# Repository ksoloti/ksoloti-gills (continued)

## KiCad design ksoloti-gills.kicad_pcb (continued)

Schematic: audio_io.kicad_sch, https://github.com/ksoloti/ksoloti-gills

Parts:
J3: IN_L; Jack_6.35mm_Neutrik_NRJ6HF_Horizontal_no_screwhole
J4: IN_R; Jack_6.35mm_Neutrik_NRJ6HF_Horizontal_no_screwhole
J5: OUT_L; Jack_6.35mm_Neutrik_NRJ6HF_Horizontal_no_screwhole
J6: OUT_R; Jack_6.35mm_Neutrik_NRJ6HF_Horizontal_no_screwhole
J7: HP_OUT; Jack_6.35mm_Neutrik_NRJ6HF_Horizontal_no_screwhole
J14: HP_POT; PinHeader_2x03_P2.54mm_Vertical
J19: OUTPUT_INSERT; PinHeader_1x05_P2.54mm_Vertical
JP2: LR_NORMAL; SolderJumper-2_0603_Bridged_0_25mm
R22, R23, R24, R33: 220; R_0603_1608Metric
R25, R34, R56, R57: 47k; R_0603_1608Metric
RV11, RV12: 2*B100k; ALPS_POT_VERTICAL_PS_DUAL
TP1: OUT_L_RING; TestPoint_THTPad_D1.5mm_Drill0.7mm
TP2: OUT_R_RING; TestPoint_THTPad_D1.5mm_Drill0.7mm

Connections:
GND: RV11.7, RV12.7; also elsewhere on the board
IN_L_PIN: R56.2, RV11.2; also elsewhere on the board
IN_R_PIN: R57.2, RV11.5; also elsewhere on the board
IN_SGND_PIN: J3.S, J3.SN, J4.S, J4.SN, R56.1, R57.1, RV11.1, RV11.4; also elsewhere on the board
LHP: J7.T, J14.4, J14.6; also elsewhere on the board
MONOOUT: J7.S, J14.1, J14.2; also elsewhere on the board
unnamed: J4.T, RV11.6
unnamed: J5.R, R22.2
unnamed: J5.T, R23.2
unnamed: J6.R, R24.2
unnamed: J6.T, R33.2
unnamed: J4.TN, JP2.1 (A)
unnamed: J3.T, JP2.2 (B), RV11.3
unnamed: R22.1, TP1.1
unnamed: R23.1, R25.2, RV12.2
unnamed: R24.1, TP2.1
unnamed: R33.1, R34.2, RV12.5
OUT_L_PIN: J19.4, J19.5, RV12.3; also elsewhere on the board
OUT_R_PIN: J19.1, J19.2, RV12.6; also elsewhere on the board
OUT_SGND_PIN: J5.S, J5.SN, J6.S, J6.SN, J19.3, R25.1, R34.1, RV12.1, RV12.4; also elsewhere on the board
RHP: J7.R, J14.3, J14.5; also elsewhere on the board

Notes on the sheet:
R->
L->
HEADPHONES
output attenuator
If installing a headphone volume pot, cut bridges between pins 3&5 and 4&6!
OPTIONAL HP VOLUME
OUTPUT
INPUT
Pot "chassis"
Audio I/O
input attenuator

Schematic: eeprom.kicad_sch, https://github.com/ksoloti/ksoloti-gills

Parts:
C9: 100n; C_0603_1608Metric
U1: M24512; SOIC-8_3.9x4.9mm_P1.27mm

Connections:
+3.3V: C9.1, U1.8 (VCC); also elsewhere on the board
GND: C9.2, U1.1 (E0), U1.2 (E1), U1.3 (E2), U1.4 (VSS), U1.7 (~WC); also elsewhere on the board
PB8_GPDIO: U1.6 (SCL); also elsewhere on the board
PB9_GPDIO: U1.5 (SDA); also elsewhere on the board

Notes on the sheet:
M24512-W SOIC-8

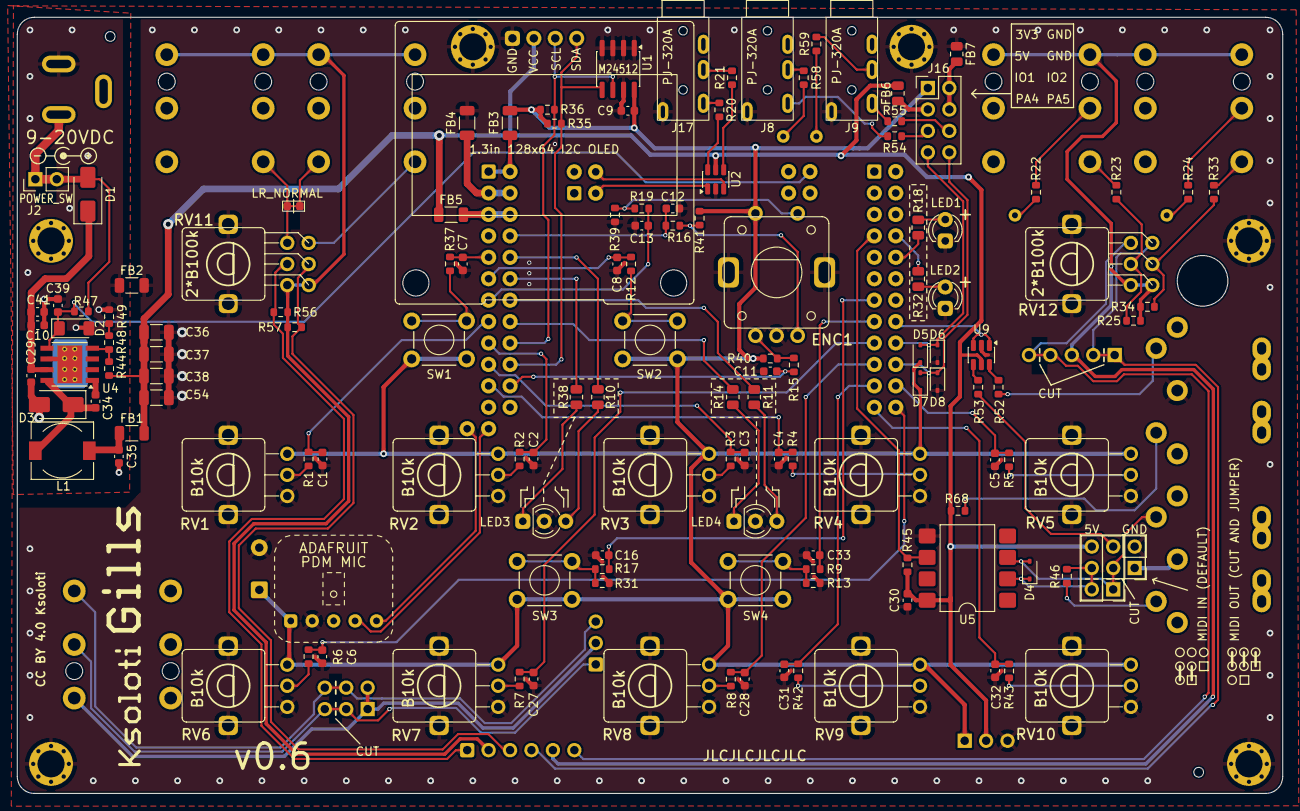
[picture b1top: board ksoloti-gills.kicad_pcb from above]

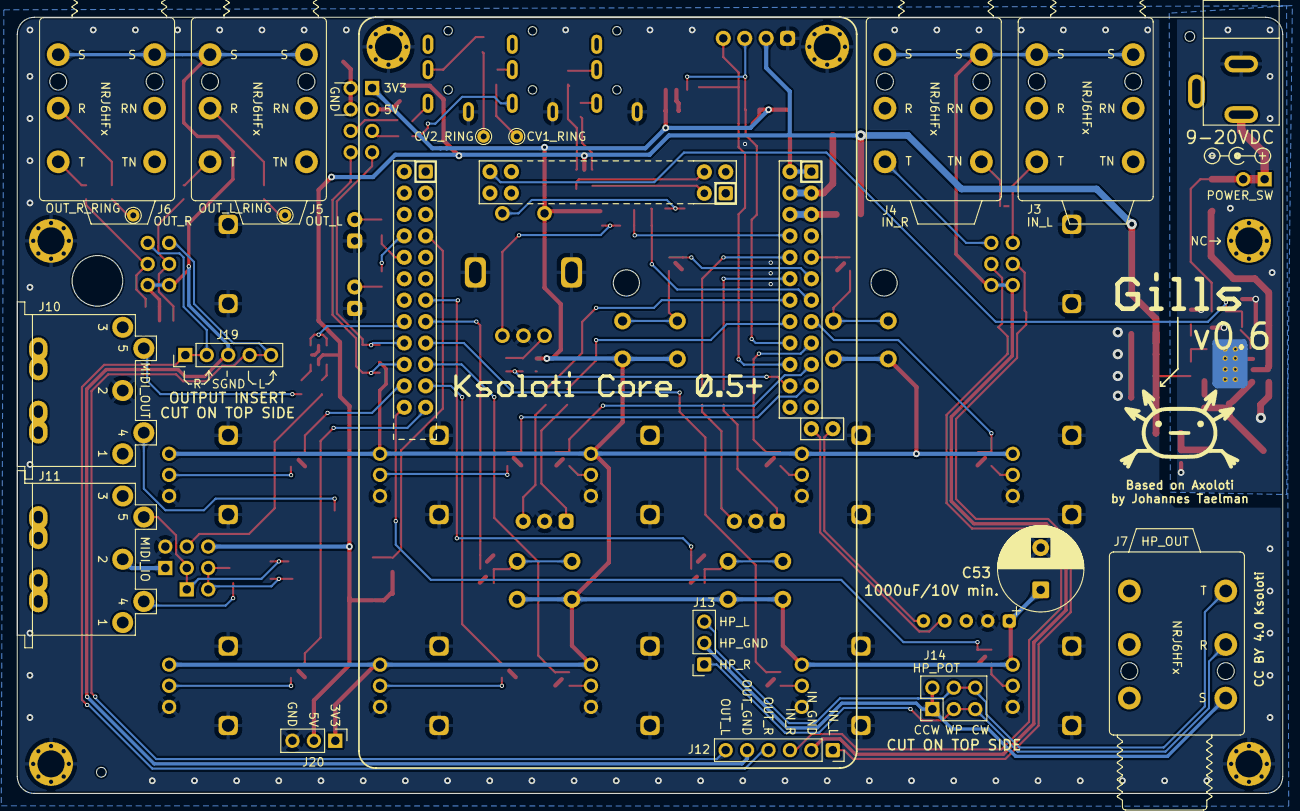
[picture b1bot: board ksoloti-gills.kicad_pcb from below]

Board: 2 copper layers, 150.0 x 92.0 mm, 224 parts (78 on the bottom side), 114 nets.

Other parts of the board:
DUMMY_CORE_3DMODEL: Symbol_Barrel_Polarity
DUMMY_CV_EXP_3DMODEL: Symbol_Barrel_Polarity
G513513: LOGO
LOGO1, LOGO2: Symbol_Barrel_Polarity

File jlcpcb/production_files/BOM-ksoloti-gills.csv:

Comment,Designator,Footprint,LCSC,Quantity
100 ohm @ 100 Mhz,"FB6,FB7",R_0805_2012Metric,C1015,2
100 ohm @ 100 Mhz,"FB1,FB2,FB3,FB4,FB5",R_1206_3216Metric,C98293,5
100n,"C11,C12,C13,C16,C29,C30,C33,C35,C39,C7,C8,C9",C_0603_1608Metric,C14663,12
10k,"R13,R31,R39,R40,R41,R44,R45",R_0603_1608Metric,C25804,7
10n,C34,C_0603_1608Metric,C57112,1
10u_25V,"C10,C41",C_0603_1608Metric,C96446,2
15uh,L1,L_7.3x6.7_H3.5,C2847544,1
1N4148WS,D4,D_SOD-323,C2128,1
1N5819WS,"D5,D6,D7,D8",D_SOD-323,C191023,4
1k,"R1,R12,R15,R16,R17,R19,R2,R3,R37,R4,R42,R43,R5,R6,R7,R8,R9",R_0603_1608Metric,C21190,17
2.2u,"C1,C2,C27,C28,C3,C31,C32,C4,C5,C6",C_0603_1608Metric,C23630,10
2.7k,"R35,R36",R_0603_1608Metric,C13167,2
220,"R20,R21,R22,R23,R24,R33,R46,R48,R52,R53,R54,R55,R58,R59,R68",R_0603_1608Metric,C22962,15
3V3,D2,D_MiniMELF,C7497475,1
3k,R49,R_0603_1608Metric,C4211,1
47k,"R25,R34,R47,R56,R57",R_0603_1608Metric,C25819,5
47u,"C36,C37,C38,C54",C_1206_3216Metric,C96123,4
6N137,U5,SMDIP-8_W9.53mm,C110020,1
74LVC2G17,"U2,U9",SOT-23-6,C10429,2
M24512,U1,SOIC-8_3.9x4.9mm_P1.27mm,C79991,1
RGREEN,"R10,R11,R18",R_0805_2012Metric,C17630,3
RRED,"R14,R32,R38",R_0805_2012Metric,C17557,3
SS34,"D1,D3",D_SMA,C8678,2
TPS5430DDA,U4,TI_SO-PowerPAD-8_ThermalVias,C9864,1
MountingHole,MH7,MountingHole_3.2mm_M3_Pad_Via_tight,,1
MountingHole,MH8,MountingHole_3.2mm_M3_Pad_Via_tight,,1
MountingHole,MH5,MountingHole_3.2mm_M3_Pad_Via_tight,,1
MountingHole,MH6,MountingHole_3.2mm_M3_Pad_Via_tight,,1
B10k,RV1,ALPS_POT_VERTICAL_PS,,1
LED_Dual_AKA,LED3,LED_D3.0mm-3_marked,,1
B10k,RV4,ALPS_POT_VERTICAL_PS,,1
LINE_IN_OUT,J12,PinSocket_1x06_P2.54mm_Vertical,,1
LED_Dual_AKA,LED4,LED_D3.0mm-3_marked,,1
B10k,RV2,ALPS_POT_VERTICAL_PS,,1
2*B100k,RV11,ALPS_POT_VERTICAL_PS_DUAL,,1
HP_POT,J14,PinHeader_2x03_P2.54mm_Vertical,,1
TL1105,SW1,TL1105T,,1
TL1105,SW4,TL1105T,,1
TL1105,SW2,TL1105T,,1
B10k,RV3,ALPS_POT_VERTICAL_PS,,1
MIDI_IO,J11,MIDI_DIN-5_DS-5-01c,,1
B10k,RV10,ALPS_POT_VERTICAL_PS,,1
B10k,RV9,ALPS_POT_VERTICAL_PS,,1
B10k,RV6,ALPS_POT_VERTICAL_PS,,1
MountingHole,MH4,MountingHole_3.2mm_M3_Pad_Via_tight,,1
2*B100k,RV12,ALPS_POT_VERTICAL_PS_DUAL,,1
RED,LED2,LED_D3.0mm_marked,,1
STEC11,ENC1,ALPS_STEC12E08,,1
B10k,RV7,ALPS_POT_VERTICAL_PS,,1
TL1105,SW3,TL1105T,,1
B10k,RV5,ALPS_POT_VERTICAL_PS,,1
MountingHole,MH1,MountingHole_3.2mm_M3_Pad_Via_tight,,1
B10k,RV8,ALPS_POT_VERTICAL_PS,,1
HP_OUT,J13,PinSocket_1x03_P2.54mm_Vertical,,1
128x64_OLED,OLED1,128x64OLED_1_3in,,1
GREEN,LED1,LED_D3.0mm_marked,,1
IN_L,J3,Jack_6.35mm_Neutrik_NRJ6HF_Horizontal_no_screwhole,,1
Conn_01x01_Female,H2_P21,PinSocket_1x01_P2.54mm_Vertical_smcrt_round,,1
Conn_01x01_Female,H1_P12,PinSocket_1x01_P2.54mm_Vertical_smcrt_round,,1
Conn_01x01_Female,H3_P2,PinSocket_1x01_P2.54mm_Vertical_smcrt_round,,1
Conn_01x01_Female,H1_P13,PinSocket_1x01_P2.54mm_Vertical_smcrt_round,,1
Conn_01x01_Female,H3_P4,PinSocket_1x01_P2.54mm_Vertical_smcrt_round,,1
Conn_01x01_Female,H1_P22,PinSocket_1x01_P2.54mm_Vertical_smcrt_round,,1
Conn_01x01_Female,H3_P17,PinSocket_1x01_P2.54mm_Vertical_smcrt_round,,1
Conn_01x01_Female,H3_P19,PinSocket_1x01_P2.54mm_Vertical_smcrt_round,,1
HP_OUT,J7,Jack_6.35mm_Neutrik_NRJ6HF_Horizontal_no_screwhole,,1
OUT_R,J6,Jack_6.35mm_Neutrik_NRJ6HF_Horizontal_no_screwhole,,1
Conn_01x01_Female,H3_P22,PinSocket_1x01_P2.54mm_Vertical_smcrt_round,,1
Conn_01x01_Female,H3_P15,PinSocket_1x01_P2.54mm_Vertical_smcrt_round,,1
EXP_IO,J8,PJ-320A_THT,,1
MIDI_OUT,J10,MIDI_DIN-5_DS-5-01c,,1
Conn_01x01_Female,H3_P23,PinSocket_1x01_P2.54mm_Vertical_smcrt_round,,1
Conn_01x01_Female,H3_P16,PinSocket_1x01_P2.54mm_Vertical_smcrt_round,,1
Conn_01x01_Female,H1_P17,PinSocket_1x01_P2.54mm_Vertical_smcrt_round,,1
Conn_01x01_Female,H3_P8,PinSocket_1x01_P2.54mm_Vertical_smcrt_round,,1
Conn_01x01_Female,H3_P14,PinSocket_1x01_P2.54mm_Vertical_smcrt_round,,1
Conn_01x01_Female,H1_P23,PinSocket_1x01_P2.54mm_Vertical_smcrt_round,,1
Conn_01x01_Female,H2_P23,PinSocket_1x01_P2.54mm_Vertical_smcrt_round,,1
Conn_01x01_Female,H3_P11,PinSocket_1x01_P2.54mm_Vertical_smcrt_round,,1
Conn_01x01_Female,H2_P22,PinSocket_1x01_P2.54mm_Vertical_smcrt_round,,1
Conn_01x01_Female,H1_P18,PinSocket_1x01_P2.54mm_Vertical_smcrt_round,,1
Conn_01x01_Female,H3_P1,PinSocket_1x01_P2.54mm_Vertical_smcrt_sqr,,1
Conn_01x01_Female,H3_P24,PinSocket_1x01_P2.54mm_Vertical_smcrt_round,,1
Conn_01x01_Female,H1_P7,PinSocket_1x01_P2.54mm_Vertical_smcrt_round,,1
Conn_01x01_Female,H3_P5,PinSocket_1x01_P2.54mm_Vertical_smcrt_round,,1
Conn_01x01_Female,H3_P20,PinSocket_1x01_P2.54mm_Vertical_smcrt_round,,1
Conn_01x01_Female,H3_P21,PinSocket_1x01_P2.54mm_Vertical_smcrt_round,,1
OUT_L,J5,Jack_6.35mm_Neutrik_NRJ6HF_Horizontal_no_screwhole,,1
Conn_01x01_Female,H1_P21,PinSocket_1x01_P2.54mm_Vertical_smcrt_round,,1
9-20VDC,J1,dc_socket,,1
Conn_01x01_Female,H1_P2,PinSocket_1x01_P2.54mm_Vertical_smcrt_round,,1
Conn_01x01_Female,H1_P19,PinSocket_1x01_P2.54mm_Vertical_smcrt_round,,1
Conn_01x01_Female,H1_P9,PinSocket_1x01_P2.54mm_Vertical_smcrt_round,,1
Conn_01x01_Female,H1_P11,PinSocket_1x01_P2.54mm_Vertical_smcrt_round,,1
Conn_01x01_Female,H3_P3,PinSocket_1x01_P2.54mm_Vertical_smcrt_round,,1
Conn_01x01_Female,H1_P10,PinSocket_1x01_P2.54mm_Vertical_smcrt_round,,1
PWR_SWITCH,J2,PinHeader_1x02_P2.54mm_Vertical,,1
Conn_01x01_Female,H1_P3,PinSocket_1x01_P2.54mm_Vertical_smcrt_round,,1
Conn_01x01_Female,H2_P24,PinSocket_1x01_P2.54mm_Vertical_smcrt_round,,1
Conn_01x01_Female,H3_P10,PinSocket_1x01_P2.54mm_Vertical_smcrt_round,,1
Conn_01x01_Female,H1_P8,PinSocket_1x01_P2.54mm_Vertical_smcrt_round,,1
Conn_01x01_Female,H3_P18,PinSocket_1x01_P2.54mm_Vertical_smcrt_round,,1
Conn_01x01_Female,H3_P7,PinSocket_1x01_P2.54mm_Vertical_smcrt_round,,1
Conn_01x01_Female,H3_P12,PinSocket_1x01_P2.54mm_Vertical_smcrt_round,,1
Conn_01x01_Female,H1_P15,PinSocket_1x01_P2.54mm_Vertical_smcrt_round,,1
EXP_IO,J9,PJ-320A_THT,,1
Conn_01x01_Female,H3_P9,PinSocket_1x01_P2.54mm_Vertical_smcrt_round,,1
Conn_01x01_Female,H1_P6,PinSocket_1x01_P2.54mm_Vertical_smcrt_round,,1
Conn_01x01_Female,H1_P20,PinSocket_1x01_P2.54mm_Vertical_smcrt_round,,1
Conn_01x01_Female,H1_P4,PinSocket_1x01_P2.54mm_Vertical_smcrt_round,,1
Conn_01x01_Female,H1_P24,PinSocket_1x01_P2.54mm_Vertical_smcrt_round,,1
IN_R,J4,Jack_6.35mm_Neutrik_NRJ6HF_Horizontal_no_screwhole,,1
Conn_01x01_Female,H3_P6,PinSocket_1x01_P2.54mm_Vertical_smcrt_round,,1
Conn_01x01_Female,H3_P13,PinSocket_1x01_P2.54mm_Vertical_smcrt_round,,1
Conn_01x01_Female,H1_P1,PinSocket_1x01_P2.54mm_Vertical_smcrt_sqr,,1
Conn_01x01_Female,H1_P14,PinSocket_1x01_P2.54mm_Vertical_smcrt_round,,1
Conn_01x01_Female,H1_P16,PinSocket_1x01_P2.54mm_Vertical_smcrt_round,,1
Conn_01x01_Female,H1_P5,PinSocket_1x01_P2.54mm_Vertical_smcrt_round,,1
LR_NORMAL,JP2,SolderJumper-2_0603_Bridged_0_25mm,,1
EXPANSION,J16,PinHeader_2x04_P2.54mm_Vertical,,1
MIDI1_CFG,J15,PinHeader_2x03_P2.54mm_Vertical,,1
MIDI_OUT_GND,J18,PinHeader_1x02_P2.54mm_Vertical,,1
2200u 10+V,C53,CP_Radial_D10.0mm_P5.00mm,,1
OUTPUT_INSERT,J19,PinHeader_1x05_P2.54mm_Vertical,,1
Adafruit_PDM_microphone_breakout,M1,Adafruit PDM microphone breakout,,1
POWER_HEADER,J20,PinHeader_1x03_P2.54mm_Vertical,,1
DMIC_CLK,H6_P2,PinSocket_1x01_P2.54mm_Vertical_smcrt_round,,1
DMIC_DAT,H6_P1,PinSocket_1x01_P2.54mm_Vertical_smcrt_round,,1
GATE_OUT,J17,PJ-320A_THT,,1
Conn_01x01_Female,H2_P4,PinSocket_1x01_P2.54mm_Vertical_smcrt_round,,1
Conn_01x01_Female,H2_P3,PinSocket_1x01_P2.54mm_Vertical_smcrt_round,,1
Conn_01x01_Female,H2_P2,PinSocket_1x01_P2.54mm_Vertical_smcrt_round,,1
Conn_01x01_Female,H2_P1,PinSocket_1x01_P2.54mm_Vertical_smcrt_sqr,,1

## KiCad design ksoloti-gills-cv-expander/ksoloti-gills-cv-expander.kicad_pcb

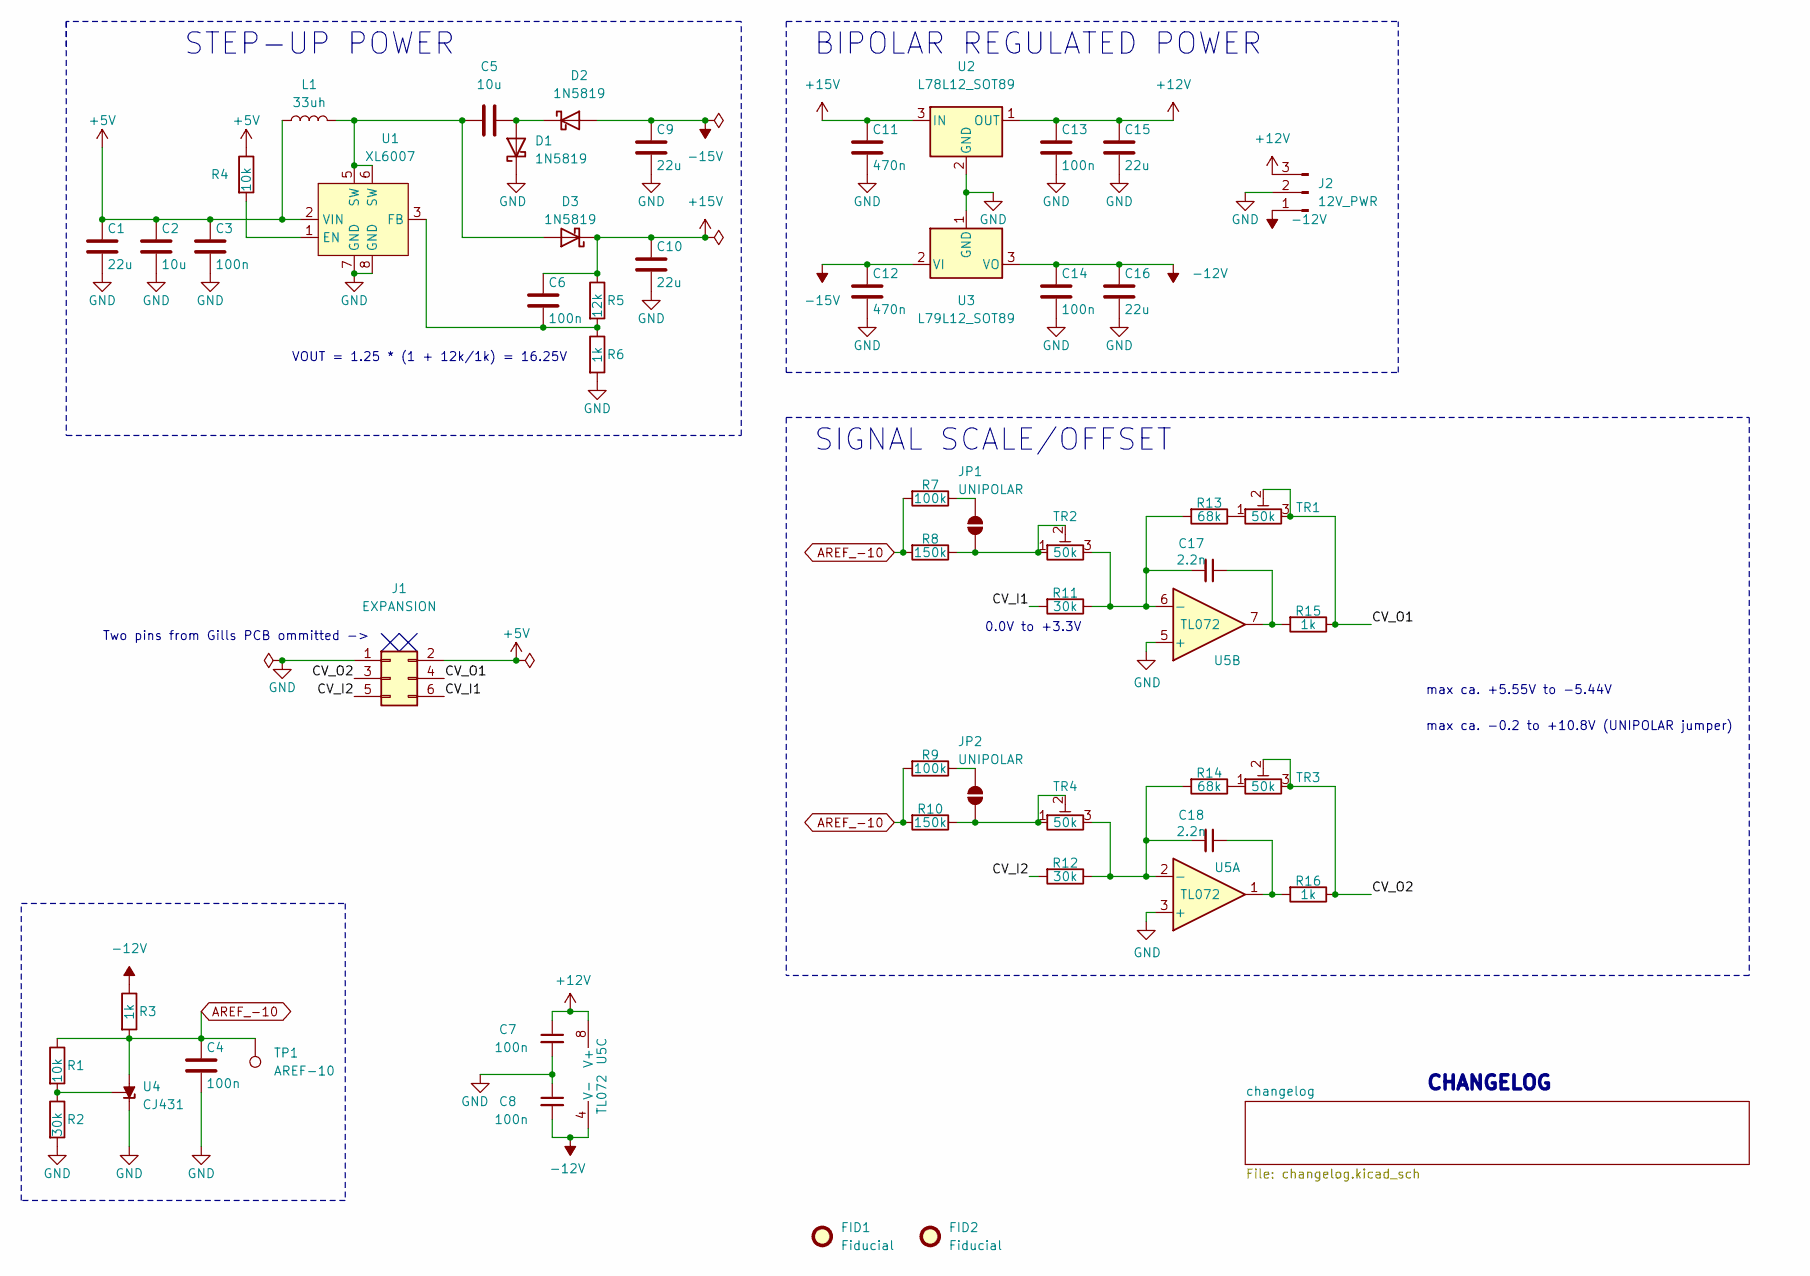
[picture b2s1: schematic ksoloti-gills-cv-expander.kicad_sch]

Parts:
C1, C9, C10, C15, C16: 22u; C_0805_2012Metric
C2, C5: 10u; C_0603_1608Metric
C3, C4, C6, C7, C8, C13, C14: 100n; C_0603_1608Metric
C11, C12: 470n; C_0603_1608Metric
C17, C18: 2.2n; C_0603_1608Metric
D1, D2, D3: 1N5819; D_SOD-323
FID1, FID2: Fiducial; jlc_tooling_hole
J1: EXPANSION; PinHeader_2x03_P2.54mm_Vertical
J2: 12V_PWR; PinHeader_1x03_P2.54mm_Vertical
JP1, JP2: UNIPOLAR; SolderJumper-2_0603_Open
L1: 33uh; L_APV_ANR5020
R1, R4: 10k; R_0603_1608Metric
R2, R11, R12: 30k; R_0603_1608Metric
R3, R6, R15, R16: 1k; R_0603_1608Metric
R5: 12k; R_0603_1608Metric
R7, R9: 100k; R_0603_1608Metric
R8, R10: 150k; R_0603_1608Metric
R13, R14: 68k; R_0603_1608Metric
TP1: AREF-10; TestPoint_THTPad_D1.0mm_Drill0.5mm
TR1, TR2, TR3, TR4: 50k; Potentiometer_Bourns_3266P_Horizontal
U1: XL6007; SOIC-8-1EP_3.9x4.9mm_P1.27mm_EP2.41x3.81mm
U2: L78L12_SOT89; SOT-89-3_clearance
U3: L79L12_SOT89; SOT-89-3_clearance
U4: CJ431; SOT-23W
U5: TL072; SOIC-8_3.9x4.9mm_P1.27mm

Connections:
+5V: C1.1, C2.1, C3.1, J1.2, L1.1, R4.1, U1.2 (VIN)
+12V: C7.1, C13.1, C15.1, J2.3, U2.1 (OUT), U5.8 (V+)
+15V: C6.1, C10.1, C11.1, D3.1 (K), R5.1, U2.3 (IN)
-12V: C8.2, C14.1, C16.1, J2.1, R3.1, U3.3 (VO), U5.4 (V-)
-15V: C9.1, C12.1, D2.2 (A), U3.2 (VI)
/CV_I1: J1.6, R11.2
/CV_I2: J1.5, R12.2
/CV_O1: J1.4, R15.1, TR1.2, TR1.3
/CV_O2: J1.3, R16.1, TR3.2, TR3.3
AREF_-10: C4.1, R1.1, R3.2, R7.2, R8.2, R9.2, R10.2, TP1.1, U4.3 (A)
GND: C1.2, C2.2, C3.2, C4.2, C7.2, C8.1, C9.2, C10.2, C11.2, C12.2, C13.2, C14.2, C15.2, C16.2, D1.1 (K), J1.1, J2.2, R2.2, R6.2, U1.7 (GND), U1.8 (GND), U1.9 (GND), U2.2 (GND), U3.1 (GND), U4.2 (K), U5.3 (+), U5.5 (+)
unnamed: C17.1, R15.2, U5.7
unnamed: C18.1, R16.2, U5.1
unnamed: C5.2, D1.2 (A), D2.1 (K)
unnamed: C5.1, D3.2 (A), L1.2, U1.5 (SW), U1.6 (SW)
unnamed: JP1.1 (A), R8.1, TR2.1, TR2.2
unnamed: JP1.2 (B), R7.1
unnamed: JP2.1 (A), R10.1, TR4.1, TR4.2
unnamed: JP2.2 (B), R9.1
unnamed: R13.1, TR1.1
unnamed: R14.1, TR3.1
unnamed: R4.2, U1.1 (EN)
unnamed: C6.2, R5.2, R6.1, U1.3 (FB)
unnamed: R1.2, R2.1, U4.1 (REF)
unnamed: C18.2, R12.1, R14.2, TR4.3, U5.2 (-)
unnamed: C17.2, R11.1, R13.2, TR2.3, U5.6 (-)

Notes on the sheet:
max ca. +5.55V to -5.44V
0.0V to +3.3V
VOUT = 1.25 * (1 + 12k/1k) = 16.25V
SIGNAL SCALE/OFFSET
STEP-UP POWER
CHANGELOG
max ca. -0.2 to +10.8V (UNIPOLAR jumper)
Two pins from Gills PCB ommitted ->
BIPOLAR REGULATED POWER

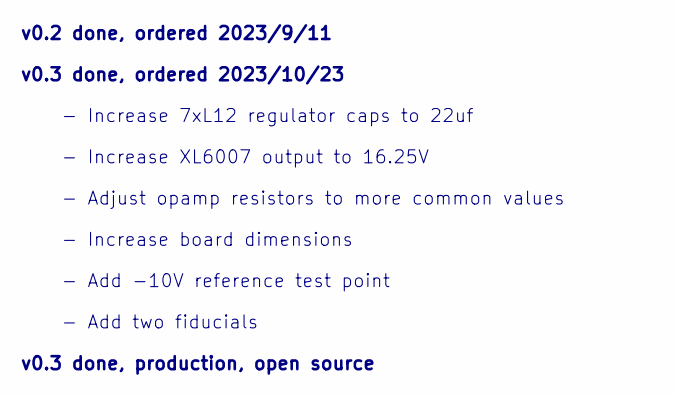
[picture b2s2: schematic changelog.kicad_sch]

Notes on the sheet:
- Increase 7xL12 regulator caps to 22uf
v0.3 done, ordered 2023/10/23
- Add -10V reference test point
- Increase XL6007 output to 16.25V
- Increase board dimensions
v0.2 done, ordered 2023/9/11
- Add two fiducials
- Adjust opamp resistors to more common values
v0.3 done, production, open source

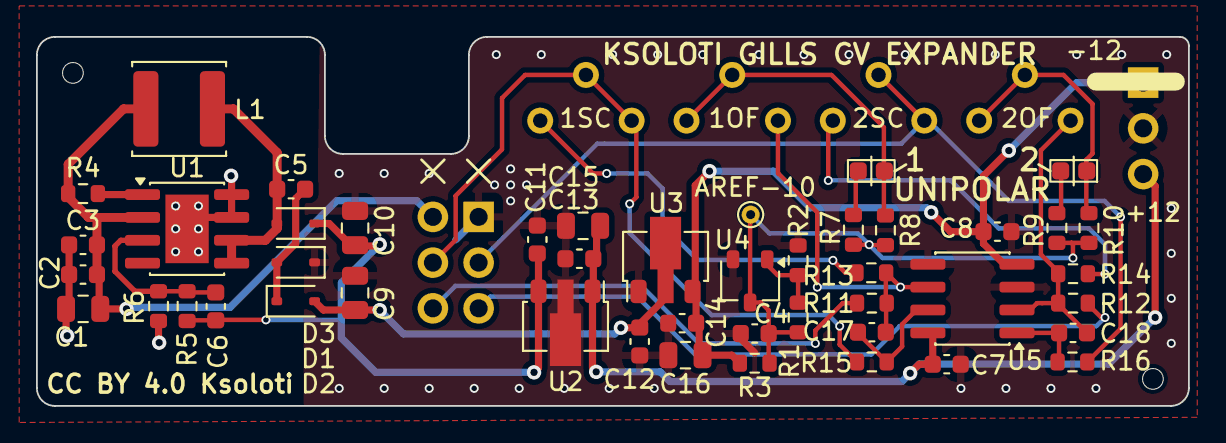
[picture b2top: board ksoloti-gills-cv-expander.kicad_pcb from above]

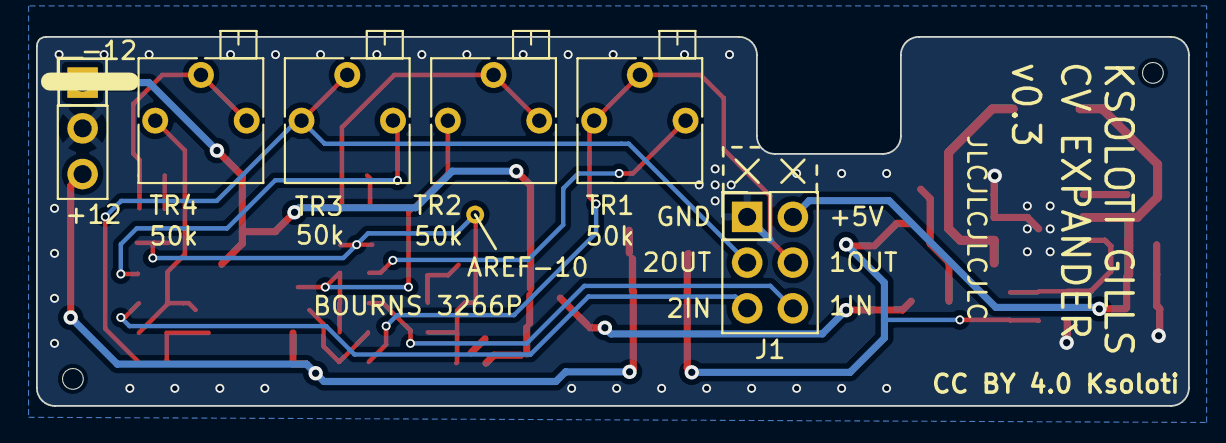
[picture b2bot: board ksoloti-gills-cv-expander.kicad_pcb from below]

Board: 2 copper layers, 64.0 x 20.5 mm, 54 parts (6 on the bottom side), 26 nets.

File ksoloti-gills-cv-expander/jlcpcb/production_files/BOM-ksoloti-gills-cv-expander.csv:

Comment,Designator,Footprint,LCSC,Quantity
100k,"R7,R9",R_0603_1608Metric,C25803,2
100n,"C13,C14,C3,C4,C6,C7,C8",C_0603_1608Metric,C14663,7
10k,"R1,R4",R_0603_1608Metric,C25804,2
10u,"C2,C5",C_0603_1608Metric,C96446,2
12k,R5,R_0603_1608Metric,C22790,1
150k,"R10,R8",R_0603_1608Metric,C22807,2
1N5819,"D1,D2,D3",D_SOD-323,C191023,3
1k,"R15,R16,R3,R6",R_0603_1608Metric,C21190,4
2.2n,"C17,C18",C_0603_1608Metric,C1604,2
22u,"C1,C10,C15,C16,C9",C_0805_2012Metric,C45783,5
30k,"R11,R12,R2",R_0603_1608Metric,C22984,3
33uh,L1,L_APV_ANR5020,C842866,1
470n,"C11,C12",C_0603_1608Metric,C1623,2
50k,"TR1,TR2,TR3,TR4",Potentiometer_Bourns_3266P_Horizontal,C123432,4
68k,"R13,R14",R_0603_1608Metric,C23231,2
CJ431,U4,SOT-23W,C3113,1
L78L12_SOT89,U2,SOT-89-3_clearance,C915681,1
L79L12_SOT89,U3,SOT-89-3_clearance,C2847004,1
TL072,U5,SOIC-8_3.9x4.9mm_P1.27mm,C6961,1
XL6007,U1,SOIC-8-1EP_3.9x4.9mm_P1.27mm_EP2.41x3.81mm,C5240411,1
12V_PWR,J2,PinHeader_1x03_P2.54mm_Vertical,,1
EXPANSION,J1,PinHeader_2x03_P2.54mm_Vertical,,1

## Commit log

2025-11-19 Update panel kicad_pro
2025-11-19 Add CV Expander project
2025-11-19 Add cv expander PDF schematic
2025-11-19 Update readmewith CV Expander schematics and BOM info
2025-11-20 Add "CC BY 4.0 Ksoloti" to silkscreens - see README
